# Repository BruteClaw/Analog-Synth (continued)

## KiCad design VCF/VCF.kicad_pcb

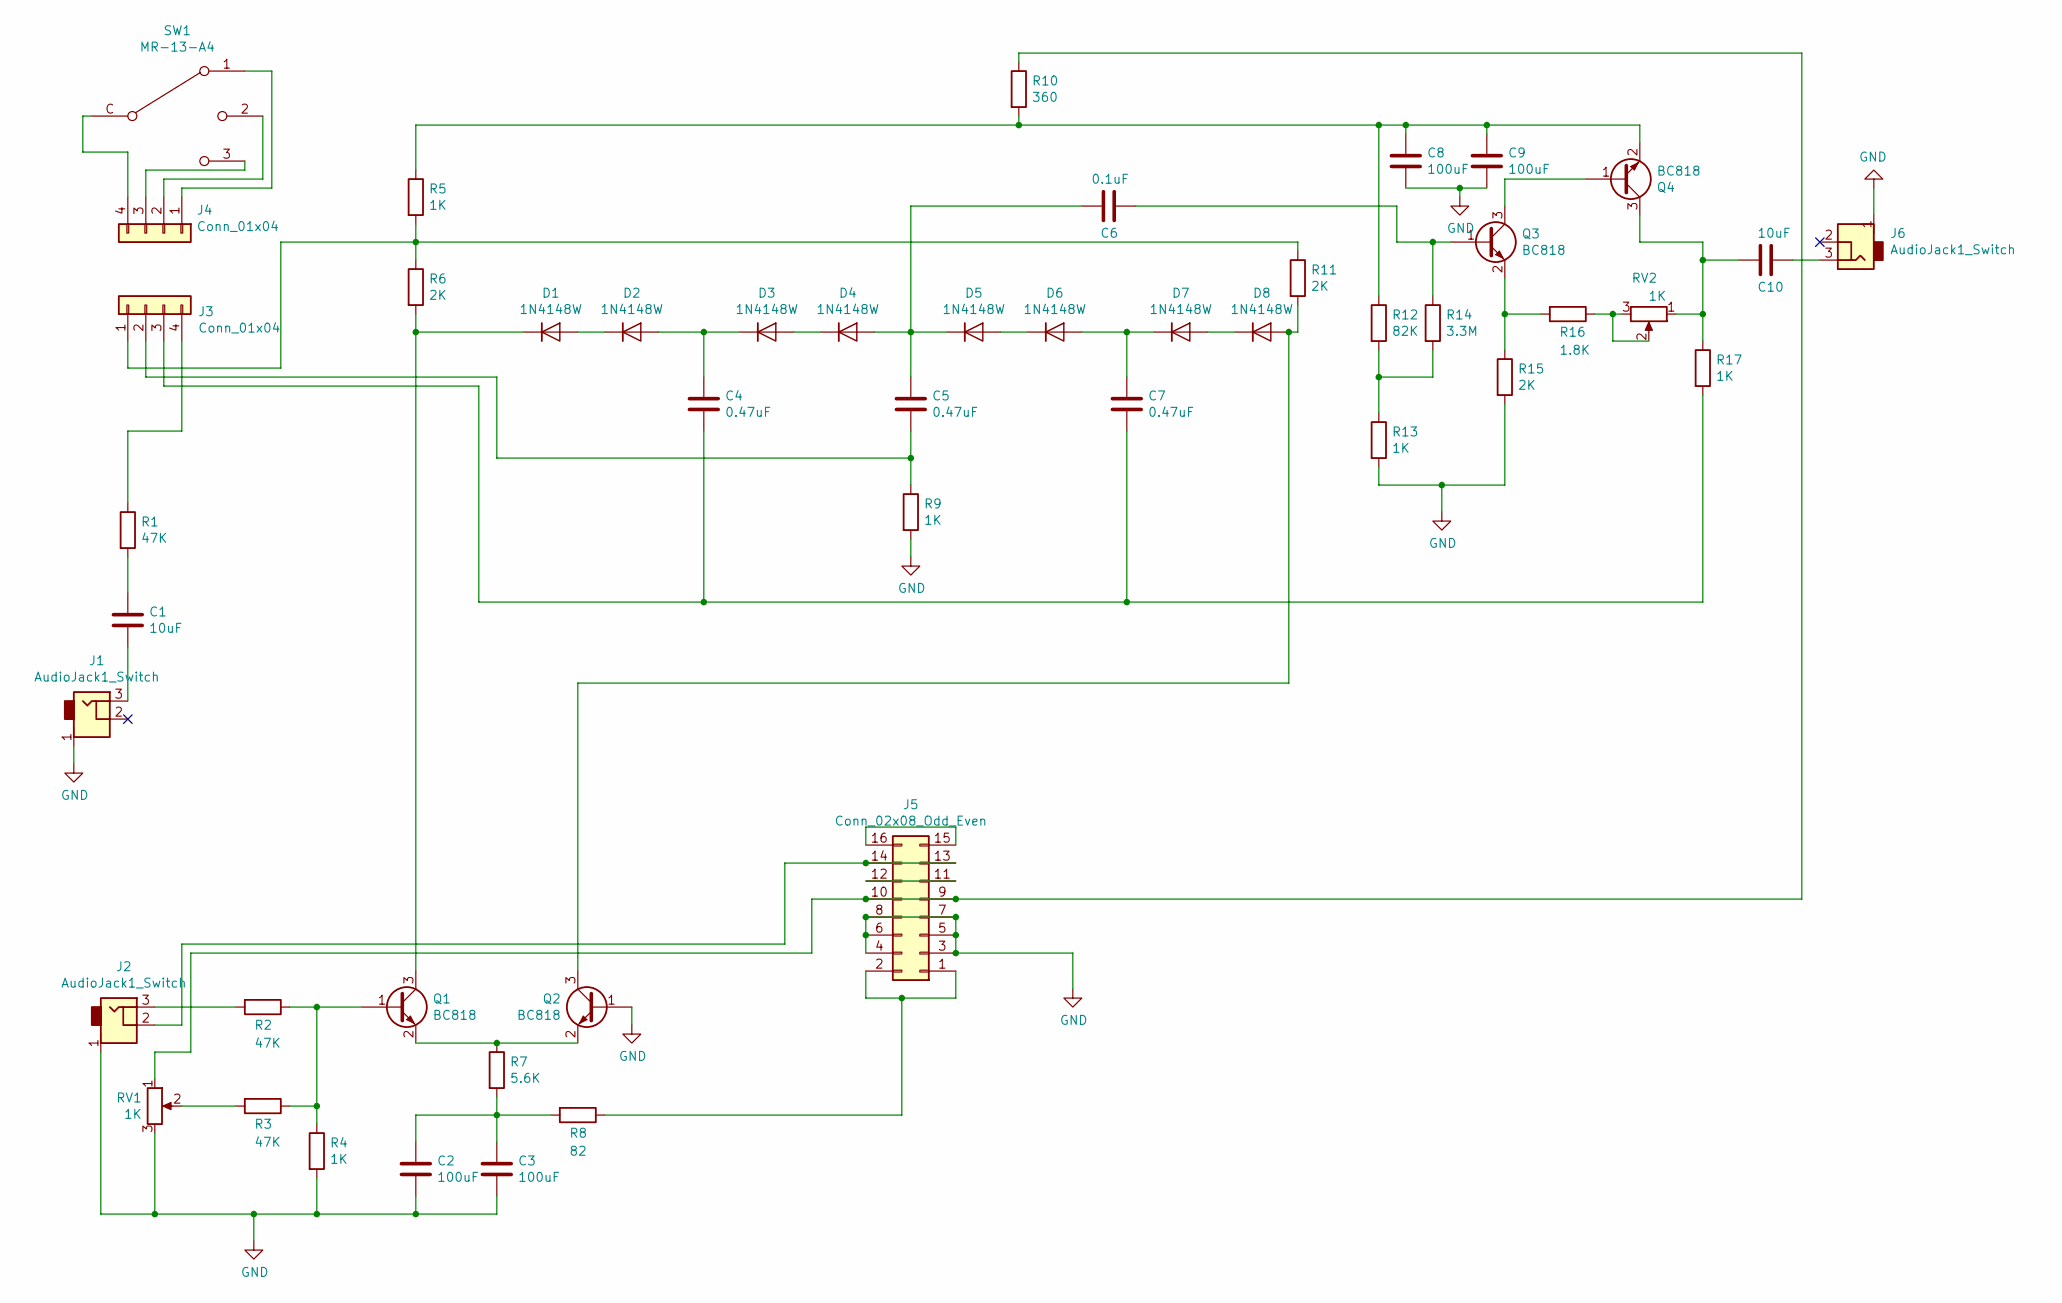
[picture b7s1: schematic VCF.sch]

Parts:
C1, C10: 10uF; C_1210_HandSoldering
C2, C3, C8, C9: 100uF; C_1210_HandSoldering
C4, C5, C7: 0.47uF; C_1210_HandSoldering
C6: 0.1uF; C_1210_HandSoldering
D1, D2, D3, D4, D5, D6, D7, D8: 1N4148W; D_SOD-123
J1, J2, J6: AudioJack1_Switch; Mono_Jack_3.5mm_Switch_Switchcraft_35RAPC2AH3
J3, J4: Conn_01x04; Pin_Header_Straight_1x04_Pitch2.54mm
J5: Conn_02x08_Odd_Even; Pin_Header_Straight_2x08_Pitch2.54mm
Q1, Q2, Q3, Q4: BC818; SOT-23
R1, R2, R3: 47K; R_1210_HandSoldering
R4, R5, R9, R13, R17: 1K; R_1210_HandSoldering
R6, R11, R15: 2K; R_1210_HandSoldering
R7: 5.6K; R_1210_HandSoldering
R8: 82; R_1210_HandSoldering
R10: 360; R_1210_HandSoldering
R12: 82K; R_1210_HandSoldering
R14: 3.3M; R_1210_HandSoldering
R16: 1.8K; R_1210_HandSoldering
RV1, RV2: 1K; Potentiometer_Bourns_PTV09A-2_Vertical
SW1: MR-13-A4

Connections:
GND: C2.2, C3.2, C8.2, C9.2, J1.1, J2.1, J5.3, J5.4, J5.5, J5.6, J5.7, J5.8, J6.1, Q2.1 (B), R4.2, R9.2, R13.2, R15.2, RV1.3
unnamed: C1.1, R1.2
unnamed: C1.2, J1.3
unnamed: C2.1, C3.1, R7.2, R8.2
unnamed: C4.1, D2.2 (A), D3.1 (K)
unnamed: C4.2, C7.2, J3.3, R17.2
unnamed: C5.1, C6.2, D4.2 (A), D5.1 (K)
unnamed: C5.2, J3.2, R9.1
unnamed: C6.1, Q3.1 (B), R14.1
unnamed: C7.1, D6.2 (A), D7.1 (K)
unnamed: C8.1, C9.1, Q4.2 (E), R5.1, R10.2, R12.1
unnamed: C10.1, J6.3
unnamed: C10.2, Q4.3 (C), R17.1, RV2.1
unnamed: D1.1 (K), Q1.3 (C), R6.2
unnamed: D1.2 (A), D2.1 (K)
unnamed: D3.2 (A), D4.1 (K)
unnamed: D5.2 (A), D6.1 (K)
unnamed: D7.2 (A), D8.1 (K)
unnamed: D8.2 (A), Q2.3 (C), R11.2
unnamed: J2.2, J5.13, J5.14
unnamed: J2.3, R2.2
unnamed: J3.1, R5.2, R6.1, R11.1
unnamed: J3.4, R1.1
unnamed: J4.1, SW1.1
unnamed: J4.2, SW1.2
unnamed: J4.3, SW1.3
unnamed: J4.4, SW1.C
unnamed: J5.1, J5.2, R8.1
unnamed: J5.9, J5.10, R10.1, RV1.1
unnamed: J5.11, J5.12
unnamed: J5.15, J5.16
unnamed: Q1.1 (B), R2.1, R3.1, R4.1
unnamed: Q1.2 (E), Q2.2 (E), R7.1
unnamed: Q3.2 (E), R15.1, R16.2
unnamed: Q3.3 (C), Q4.1 (B)
unnamed: R3.2, RV1.2
unnamed: R12.2, R13.1, R14.2
unnamed: R16.1, RV2.2, RV2.3

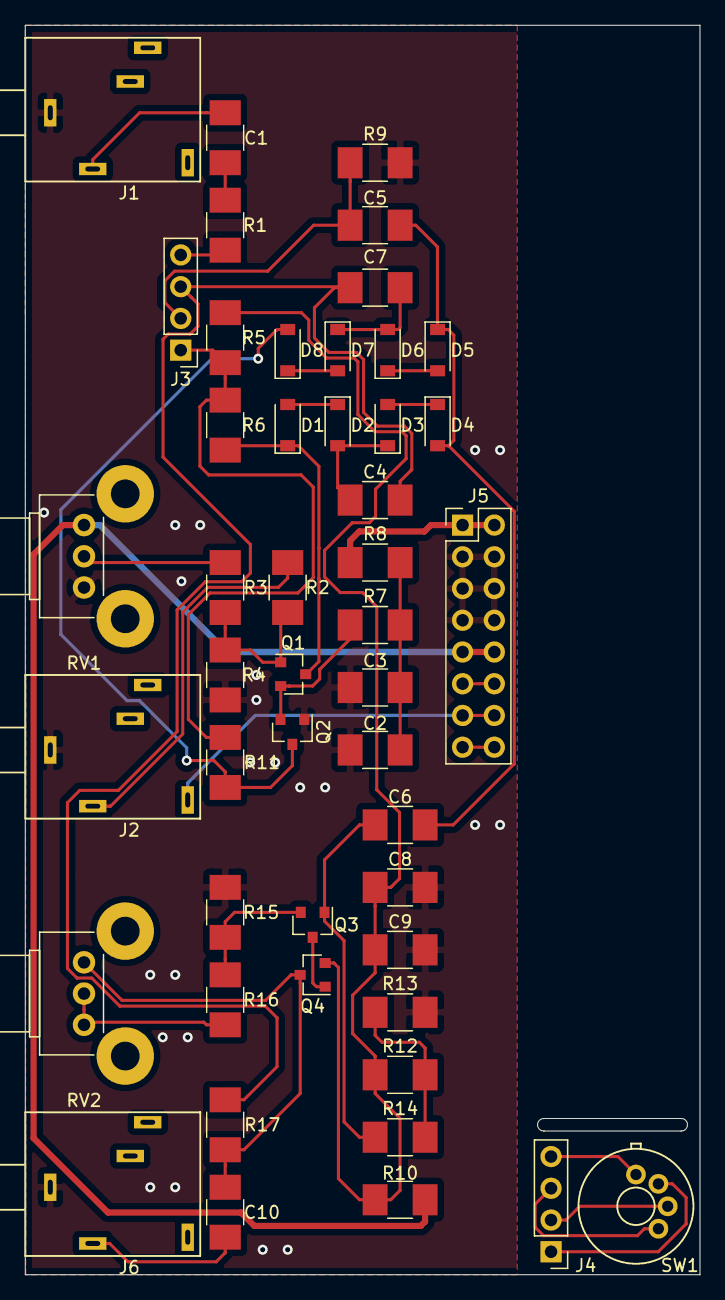
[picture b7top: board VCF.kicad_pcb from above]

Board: 2 copper layers, 54.0 x 100.0 mm, 48 parts (0 on the bottom side), 38 nets.
